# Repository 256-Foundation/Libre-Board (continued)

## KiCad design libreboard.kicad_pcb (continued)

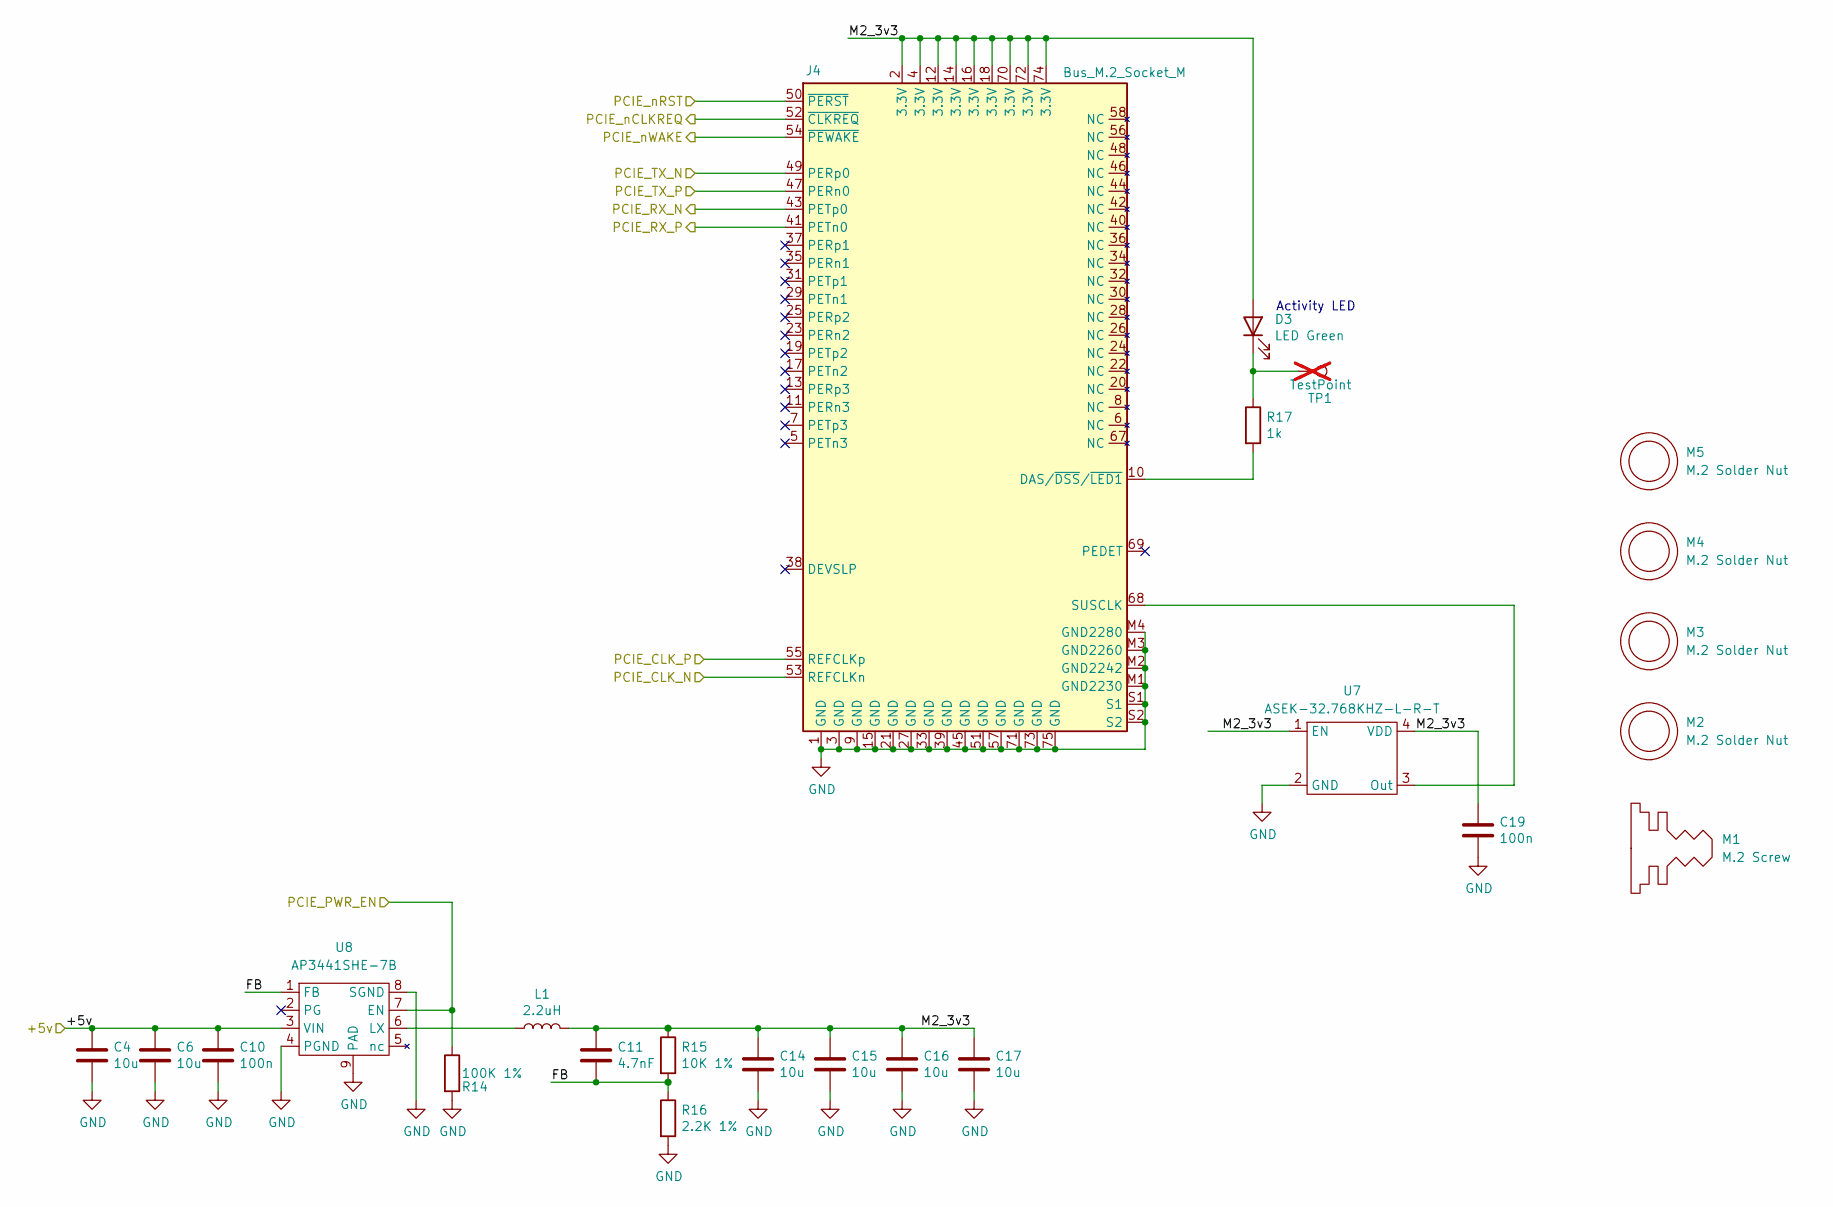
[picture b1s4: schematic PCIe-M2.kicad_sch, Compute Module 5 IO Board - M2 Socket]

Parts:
C4, C6, C14, C15, C16, C17: 10u; C_0805_2012Metric; Part Description 10uF 10% 10V Ceramic Capacitor X7R 0805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
C10, C19: 100n; C_0402_1005Metric; Part Description 0.1uF 10% 16V Ceramic Capacitor X7R 040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
C11: 4.7nF; C_0402_1005Metric; Part Description 4.7nF capacitor 0402
D3: LED Green; LED_0603_1608Metric; Part Description Green 572nm LED Indication - Discrete 2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
J4: Bus_M.2_Socket_M; M.2 M Key socket; Part Description M.2 M Key connector
L1: 2.2uH; L_Bourns_SRP5030CC; Part Description Inductor, SMT, 2520, 2u2, IRMS=7A, ISAT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
M1: M.2 Screw; Part Description M.2 Screw
M2, M3, M4, M5: M.2 Solder Nut; Part Description Solder nut for M.2 slot
R14: 100K 1%; R_0402_1005Metric; Part Description Resistor 100K M1005 1% 63mW
R15: 10K 1%; R_0402_1005Metric; Part Description Resistor 10K M1005 1% 63mW
R16: 2.2K 1%; R_0402_1005Metric; Part Description Resistor 2.2K M1005 1% 63mW
R17: 1k; R_0402_1005Metric; Part Description Resistor 1K M1005 1% 63mW
TP1: TestPoint; TestPoint_Pad_2.0x2.0mm; Part Description Test point; not fitted
U7: ASEK-32.768KHZ-L-R-T; Crystal_SMD_3225-4Pin_3.2x2.5mm; Part Description 32KHz Xtal oscilator
U8: AP3441SHE-7B; DFN-8-1EP_2x2mm_P0.5mm_EP1.05x1.75mm; Part Description 3A DC-DC converter

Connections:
/+5v: C4.1, C6.1, C10.1, U8.3 (VIN); also elsewhere on the board
/CM5_HighSpeed/PCIE_CLK_N: J4.53 (REFCLKn); also elsewhere on the board
/CM5_HighSpeed/PCIE_CLK_P: J4.55 (REFCLKp); also elsewhere on the board
/CM5_HighSpeed/PCIE_PWR_EN: R14.1, U8.7 (EN); also elsewhere on the board
/CM5_HighSpeed/PCIE_RX_N: J4.43 (PETp0); also elsewhere on the board
/CM5_HighSpeed/PCIE_RX_P: J4.41 (PETn0); also elsewhere on the board
/CM5_HighSpeed/PCIE_TX_N: J4.49 (PERp0); also elsewhere on the board
/CM5_HighSpeed/PCIE_TX_P: J4.47 (PERn0); also elsewhere on the board
/CM5_HighSpeed/PCIE_nCLKREQ: J4.52 (~CLKREQ); also elsewhere on the board
/CM5_HighSpeed/PCIE_nRST: J4.50 (~PERST); also elsewhere on the board
/CM5_HighSpeed/PCIE_nWAKE: J4.54 (~PEWAKE); also elsewhere on the board
/PCIe-M2/FB: C11.2, R15.2, R16.1, U8.1 (FB)
/PCIe-M2/M2_3v3: C11.1, C14.1, C15.1, C16.1, C17.1, C19.1, D3.2 (A), J4.2 (3.3V), J4.4 (3.3V), J4.12 (3.3V), J4.14 (3.3V), J4.16 (3.3V), J4.18 (3.3V), J4.70 (3.3V), J4.72 (3.3V), J4.74 (3.3V), L1.2, R15.1, U7.1 (EN), U7.4 (VDD)
GND: C4.2, C6.2, C10.2, C14.2, C15.2, C16.2, C17.2, C19.2, J4.1 (GND), J4.3 (GND), J4.9 (GND), J4.15 (GND), J4.21 (GND), J4.27 (GND), J4.33 (GND), J4.39 (GND), J4.45 (GND), J4.51 (GND), J4.57 (GND), J4.71 (GND), J4.73 (GND), J4.75 (GND), J4.M1 (GND2230), J4.M2 (GND2242), J4.M3 (GND2260), J4.M4 (GND2280), J4.S1, J4.S2, R14.2, R16.2, U7.2 (GND), U8.4 (PGND), U8.8 (SGND), U8.9 (PAD); also elsewhere on the board
unnamed: D3.1 (K), R17.1, TP1.1
unnamed: J4.10 (DAS/~DSS/~LED1), R17.2
unnamed: J4.68 (SUSCLK), U7.3 (Out)
unnamed: L1.1, U8.6 (LX)

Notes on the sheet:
Activity LED

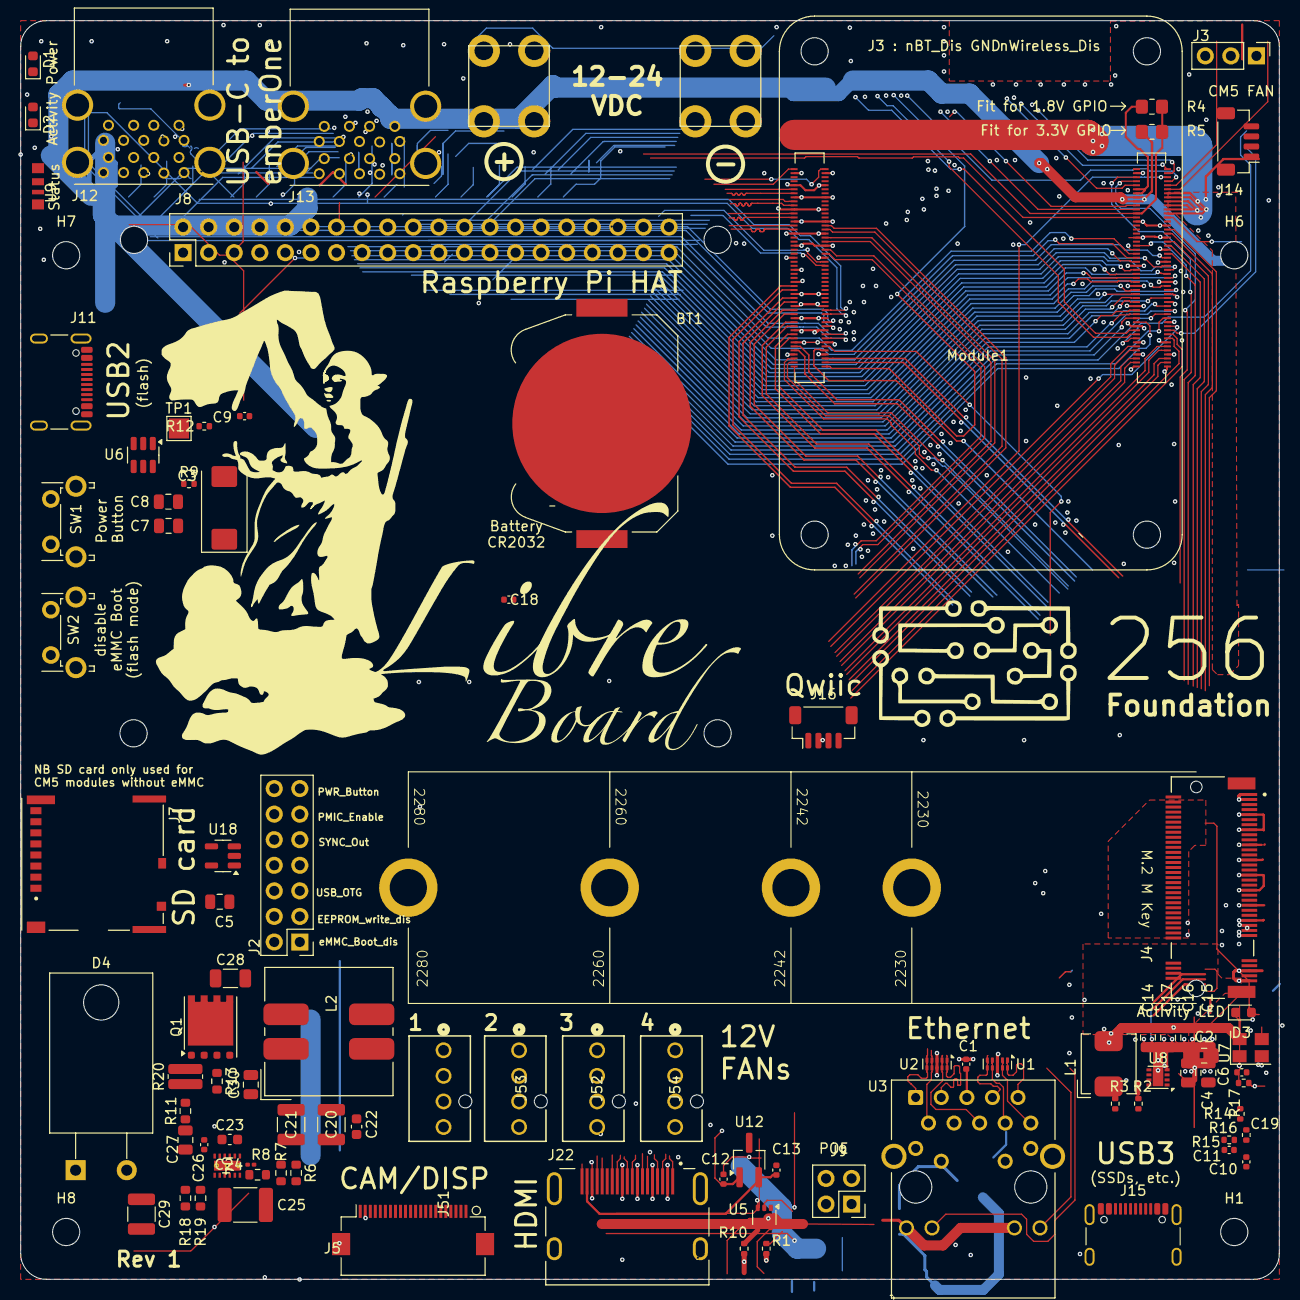
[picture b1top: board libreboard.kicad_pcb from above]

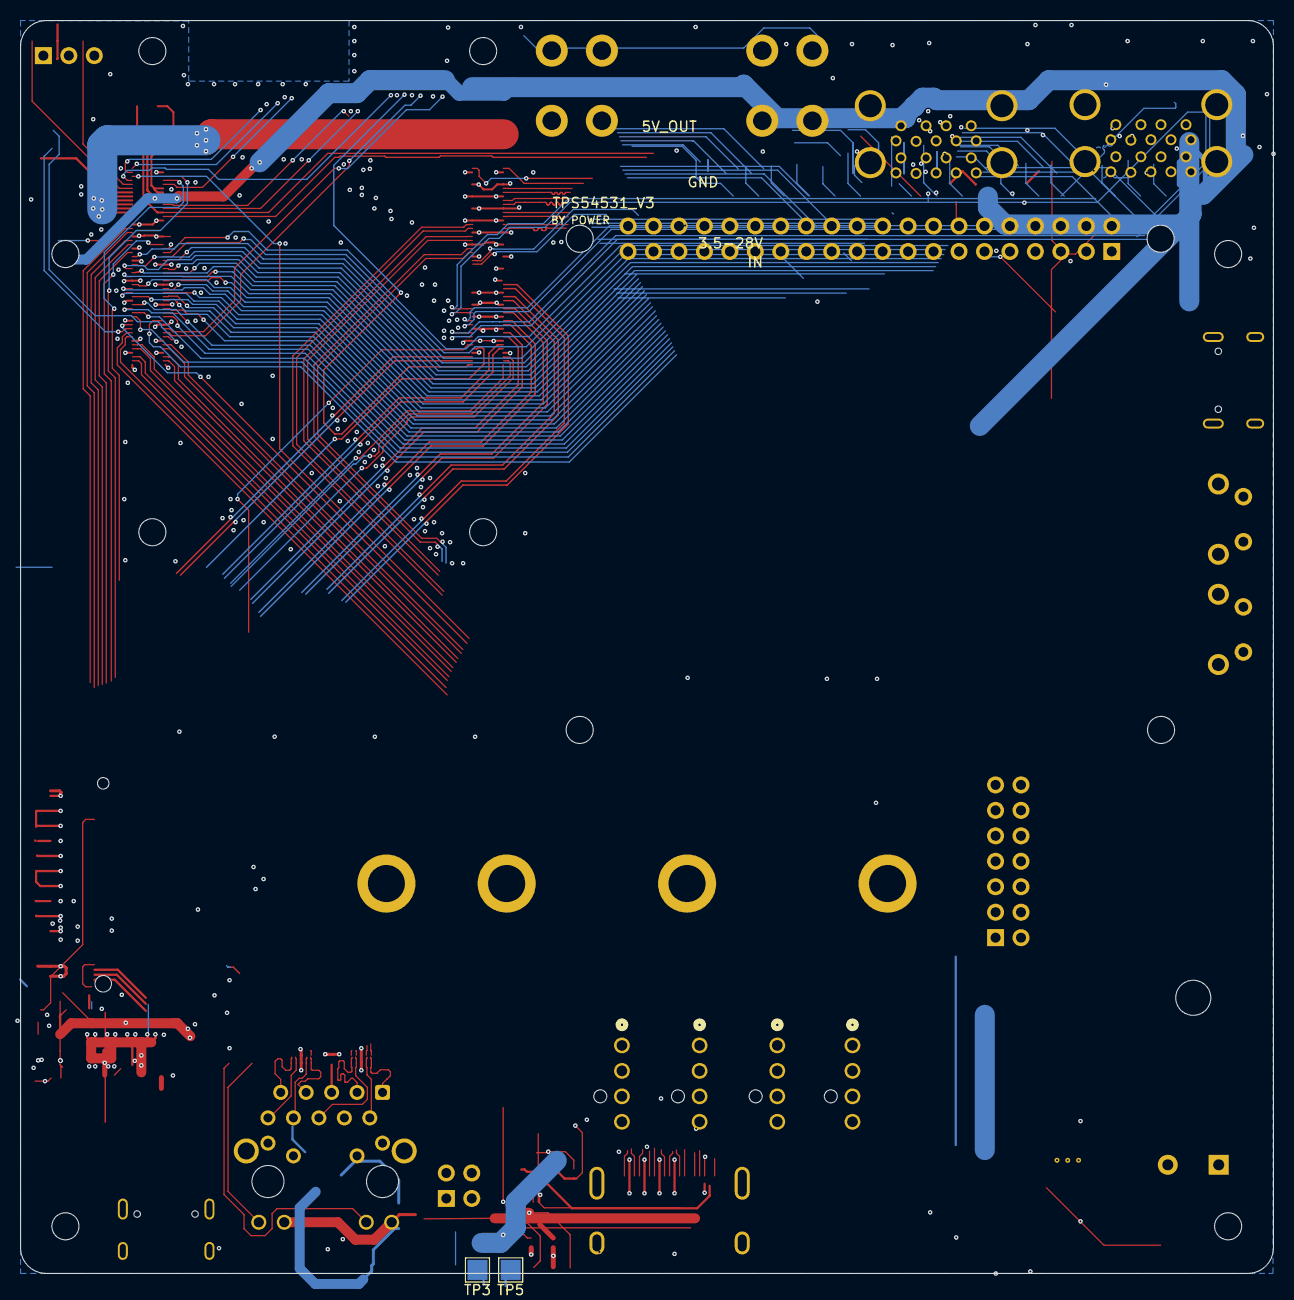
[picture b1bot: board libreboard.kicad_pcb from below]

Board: 4 copper layers, 125.0 x 125.0 mm, 103 parts (2 on the bottom side), 152 nets.

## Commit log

2025-01-27 Create LICENSE
2025-05-05 Update README.md to include additional information and images for Libre-Board
2025-06-09 first commit of kicad
2025-06-09 better 3d image which is not blue
2025-06-09 add qwicc
